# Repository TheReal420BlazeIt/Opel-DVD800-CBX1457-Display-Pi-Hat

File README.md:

# Raspberry Pi Hat for Opel DVD800 Navi Display
Raspberry Pi Hat for Opel DVD800 Navi Display using Sony CXB1457R GVIF Chip

## Project
The reason for this project is because the original radio for my car (DVD800 Navi) is quite outdated. Old navigation maps, no Bluetooth playback, etc. So the idea was to use a Raspberry Pi as a head-unit. 
Because I like the aesthetic of the original centre console of my car, I decided to reverse engineer my car's radio original display, so it can be used with the Pi. 

## Parts
All the parts are easy to get at every electronics shop. Except for the CBX1457. It was quite hard to find the chip. I ended up with ordering one from AliExpress. Quite expensive (around 35 euro's), but it works like a charm. Another option is to salvage one from a car head-unit that uses the same video chip. I ordered the PCB from JLCPCB.

CBX1457 datasheet: https://datasheetspdf.com/pdf-down/C/X/B/CXB1457R-SonyCorporation.pdf

## Raspberry Pi config.txt
The Raspberry Pi needs to be configured to output RGB video over GPIO. To enable this, we need to add a couple of lines in the config.txt on the Pi boot partition:

    gpio=0-9=a2
    gpio=12-17=a2
    gpio=20-25=a2
        
    dtoverlay=dpi18
    overscan_left=0
    overscan_right=0
    overscan_top=0
    overscan_bottom=0
    framebuffer_width=480
    framebuffer_height=240
    enable_dpi_lcd=1
    display_default_lcd=1
    dpi_group=2
    dpi_mode=87
        
    dpi_output_format=286742
        
    dpi_timings=480 0 50 12 50 240 0 6 3 10 0 0 0 60 0 9000000 3

Documentation on Raspberry Pi DPI video: https://pip.raspberrypi.com/categories/685-whitepapers-app-notes/documents/RP-003471-WP/Using-a-DPI-display.pdf

### Update:
The config.txt above doesn't work with newer versions of Raspberry Pi OS. If the above config doesn't work for you, try this one:

    gpio=0-9=a2
    gpio=12-17=a2
    gpio=20-25=a2

    dtoverlay=vc4-kms-v3d
    dtoverlay=vc4-kms-dpi-generic,hactive=480,hfp=50,hsync=12,hbp=50
    dtparam=vactive=240,vfp=6,vsync=3,vbp=10
    dtparam=clock-frequency=9000000,rgb666-padhi
    dpi_output_format=286742

## Other Vehicles
I only tested this setup on the DVD800 Navi display of an Opel Insignia. Other Opel/Vauxhall models with the same DVD800 Navi radio system should work the same (e.g. Astra/Zafira). This display uses RGB666 video input, so only 6 bits per color are used. 

This particular setup does not use bits 0 & 1 for each color on the CBX chip. For example: the Pi's red bit 0 goes to red bit 2 on the CBX chip.

The CBX1457 chip is capable of using RGB888 video, so for some vehicles this setup may be different. 

This hat may work on other car displays that use the CBX1457 transmitter in the head unit, however, the hardware/software setup may be different. The best option is to check your car's display datasheet & inspect the display driver PCB.

### Update on other displays
I successfully tested a similar display (GM part number: 23354890). Connectors and dimentions are the same, but this type has a display resolution of 800x480, so much better than the old display. Only config.txt changes are needed. Everything else works out of the box:

    gpio=0-9=a2
    gpio=12-17=a2
    gpio=20-25=a2

    dtoverlay=vc4-kms-v3d
    dtoverlay=vc4-kms-dpi-generic,hactive=800,hfp=210,hsync=1,hbp=182
    dtparam=vactive=480,vfp=62,vsync=5,vbp=6
    dtparam=clock-frequency=33300000,rgb666-padhi
    dpi_output_format=286742

## Note
Later I noticed some minor errors in the schematic:

    R7  330R needs to be 4.7K
    C9  640p needs to be 680p (Although 640p works fine. Just based on reference design)
    C10 640p needs to be 10nF

This project is tested on Raspberry Pi 4, Compute Module 4, and Compute Module 5

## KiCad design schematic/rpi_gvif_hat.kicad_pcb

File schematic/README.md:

Schematic & PCB are made with version 7.0.10. Older versions may not work!

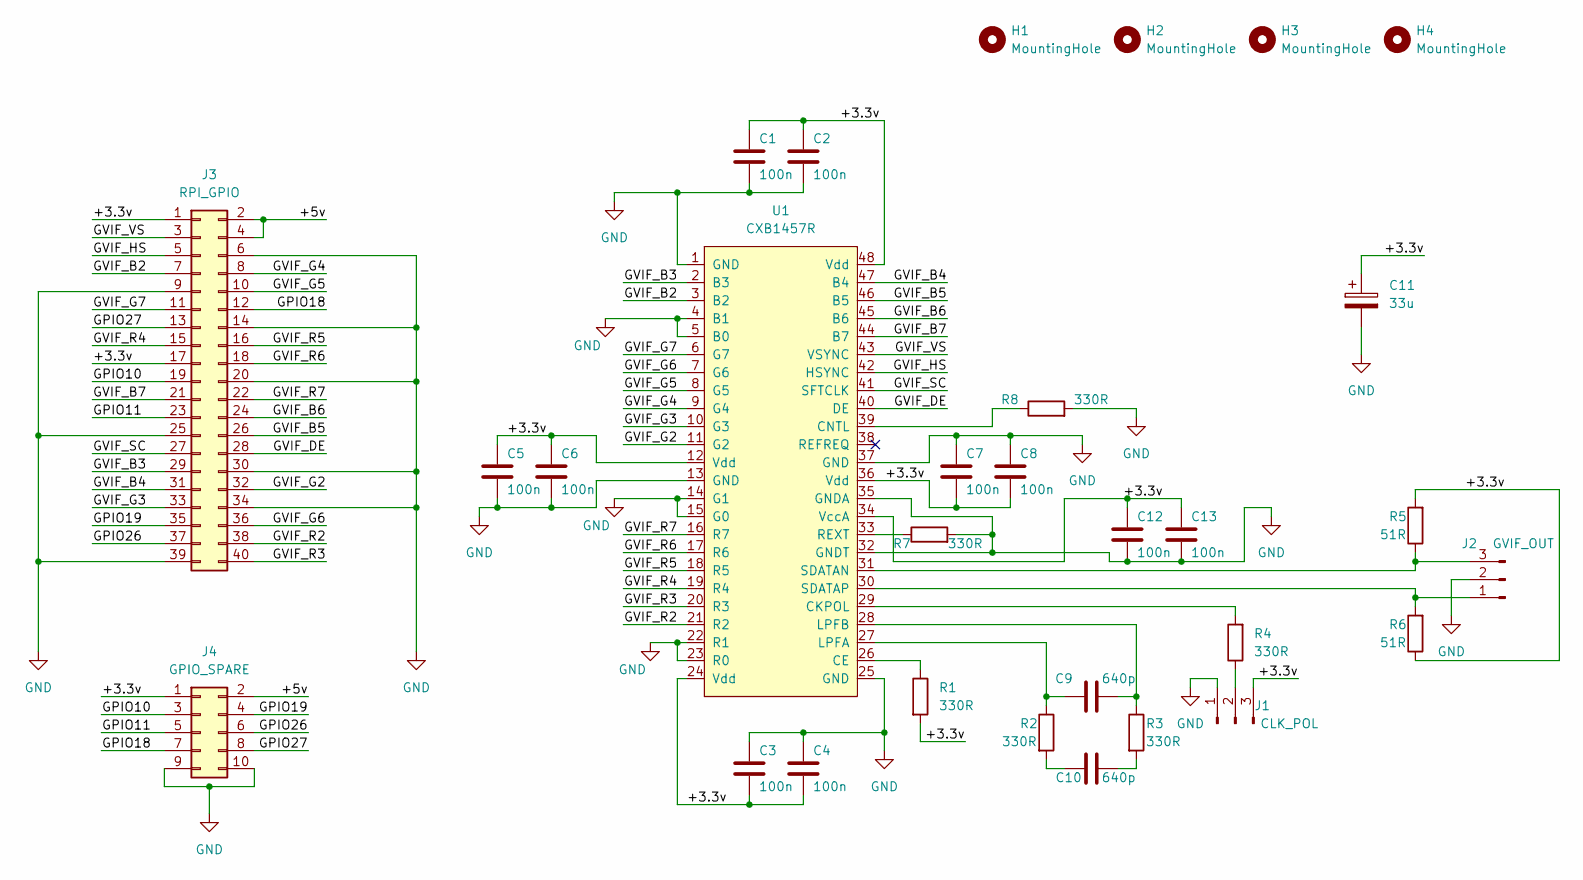
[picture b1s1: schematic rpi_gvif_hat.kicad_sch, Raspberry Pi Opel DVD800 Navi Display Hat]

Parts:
C1, C2, C3, C4, C5, C6, C7, C8, C12, C13: 100n; C_0805_2012Metric_Pad1.18x1.45mm_HandSolder
C9, C10: 640p; C_0805_2012Metric_Pad1.18x1.45mm_HandSolder
C11: 33u; CP_Elec_6.3x5.4
H1, H2, H3, H4: MountingHole; MountingHole_2.7mm_M2.5
J1: CLK_POL; PinHeader_1x03_P2.54mm_Vertical
J2: GVIF_OUT; PinHeader_1x03_P2.54mm_Vertical
J3: RPI_GPIO; PinSocket_2x20_P2.54mm_Vertical
J4: GPIO_SPARE; PinHeader_2x05_P2.54mm_Vertical
R1, R2, R3, R4, R7, R8: 330R; R_0805_2012Metric_Pad1.20x1.40mm_HandSolder
R5, R6: 51R; R_0805_2012Metric_Pad1.20x1.40mm_HandSolder
U1: CXB1457R; LQFP-48_7x7mm_P0.5mm

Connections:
/+3.3v: C1.1, C2.1, C3.2, C4.2, C5.1, C6.1, C7.2, C8.2, C11.1, C12.1, C13.1, J1.3, J3.1, J3.17, J4.1, R1.2, R5.2, R6.1, U1.12 (Vdd), U1.24 (Vdd), U1.34 (VccA), U1.36 (Vdd), U1.48 (Vdd)
/+5v: J3.2, J3.4, J4.2
/GPIO10: J3.19, J4.3
/GPIO11: J3.23, J4.5
/GPIO18: J3.12, J4.7
/GPIO19: J3.35, J4.4
/GPIO26: J3.37, J4.6
/GPIO27: J3.13, J4.8
/GVIF_B2: J3.7, U1.3 (B2)
/GVIF_B3: J3.29, U1.2 (B3)
/GVIF_B4: J3.31, U1.47 (B4)
/GVIF_B5: J3.26, U1.46 (B5)
/GVIF_B6: J3.24, U1.45 (B6)
/GVIF_B7: J3.21, U1.44 (B7)
/GVIF_DE: J3.28, U1.40 (DE)
/GVIF_G2: J3.32, U1.11 (G2)
/GVIF_G3: J3.33, U1.10 (G3)
/GVIF_G4: J3.8, U1.9 (G4)
/GVIF_G5: J3.10, U1.8 (G5)
/GVIF_G6: J3.36, U1.7 (G6)
/GVIF_G7: J3.11, U1.6 (G7)
/GVIF_HS: J3.5, U1.42 (HSYNC)
/GVIF_R2: J3.38, U1.21 (R2)
/GVIF_R3: J3.40, U1.20 (R3)
/GVIF_R4: J3.15, U1.19 (R4)
/GVIF_R5: J3.16, U1.18 (R5)
/GVIF_R6: J3.18, U1.17 (R6)
/GVIF_R7: J3.22, U1.16 (R7)
/GVIF_SC: J3.27, U1.41 (SFTCLK)
/GVIF_VS: J3.3, U1.43 (VSYNC)
GND: C1.2, C2.2, C3.1, C4.1, C5.2, C6.2, C7.1, C8.1, C11.2, C12.2, C13.2, J1.1, J2.2, J3.6, J3.9, J3.14, J3.20, J3.25, J3.30, J3.34, J3.39, J4.9, J4.10, R7.2, R8.2, U1.1 (GND), U1.4 (B1), U1.5 (B0), U1.13 (GND), U1.14 (G1), U1.15 (G0), U1.22 (R1), U1.23 (R0), U1.25 (GND), U1.32 (GNDT), U1.35 (GNDA), U1.37 (GND)
unnamed: C10.1, R2.2
unnamed: C10.2, R3.2
unnamed: J1.2, R4.1
unnamed: J2.1, R6.2, U1.30 (SDATAP)
unnamed: J2.3, R5.1, U1.31 (SDATAN)
unnamed: R1.1, U1.26 (CE)
unnamed: R4.2, U1.29 (CKPOL)
unnamed: R8.1, U1.39 (CNTL)
unnamed: C9.1, R2.1, U1.27 (LPFA)
unnamed: C9.2, R3.1, U1.28 (LPFB)
unnamed: R7.1, U1.33 (REXT)

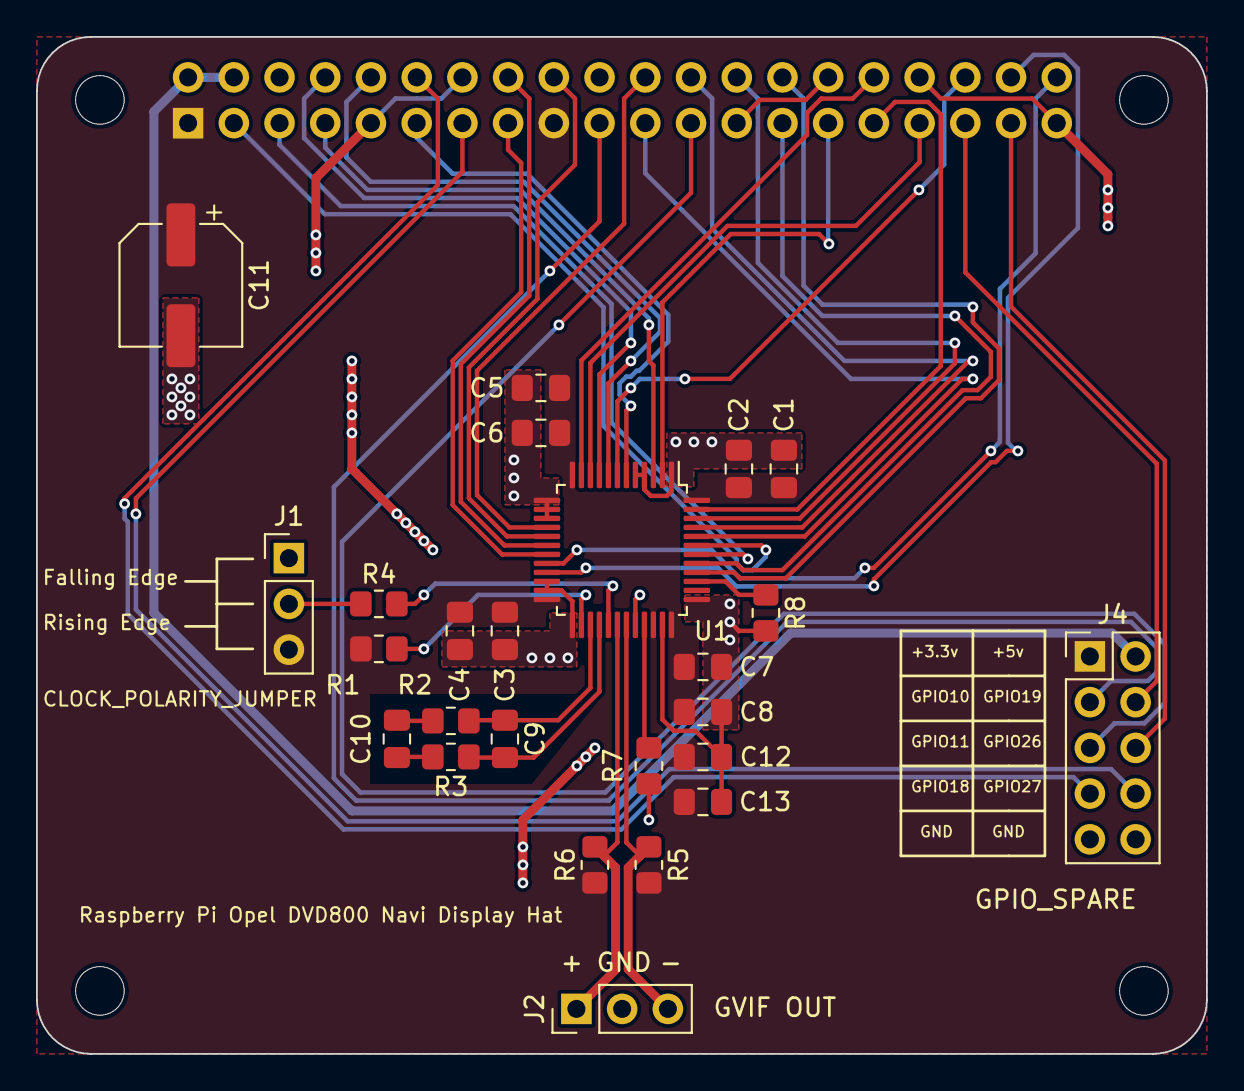
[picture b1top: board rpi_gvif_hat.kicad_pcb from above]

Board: 2 copper layers, 65.0 x 56.5 mm, 30 parts (1 on the bottom side), 42 nets.

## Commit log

2024-08-30 Added PCB and Schematic
2024-08-30 Added images
2024-08-30 Readme Update

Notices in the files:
schematic/rpi_gvif_hat.kicad_pcb:
License: GNU GPLv3
